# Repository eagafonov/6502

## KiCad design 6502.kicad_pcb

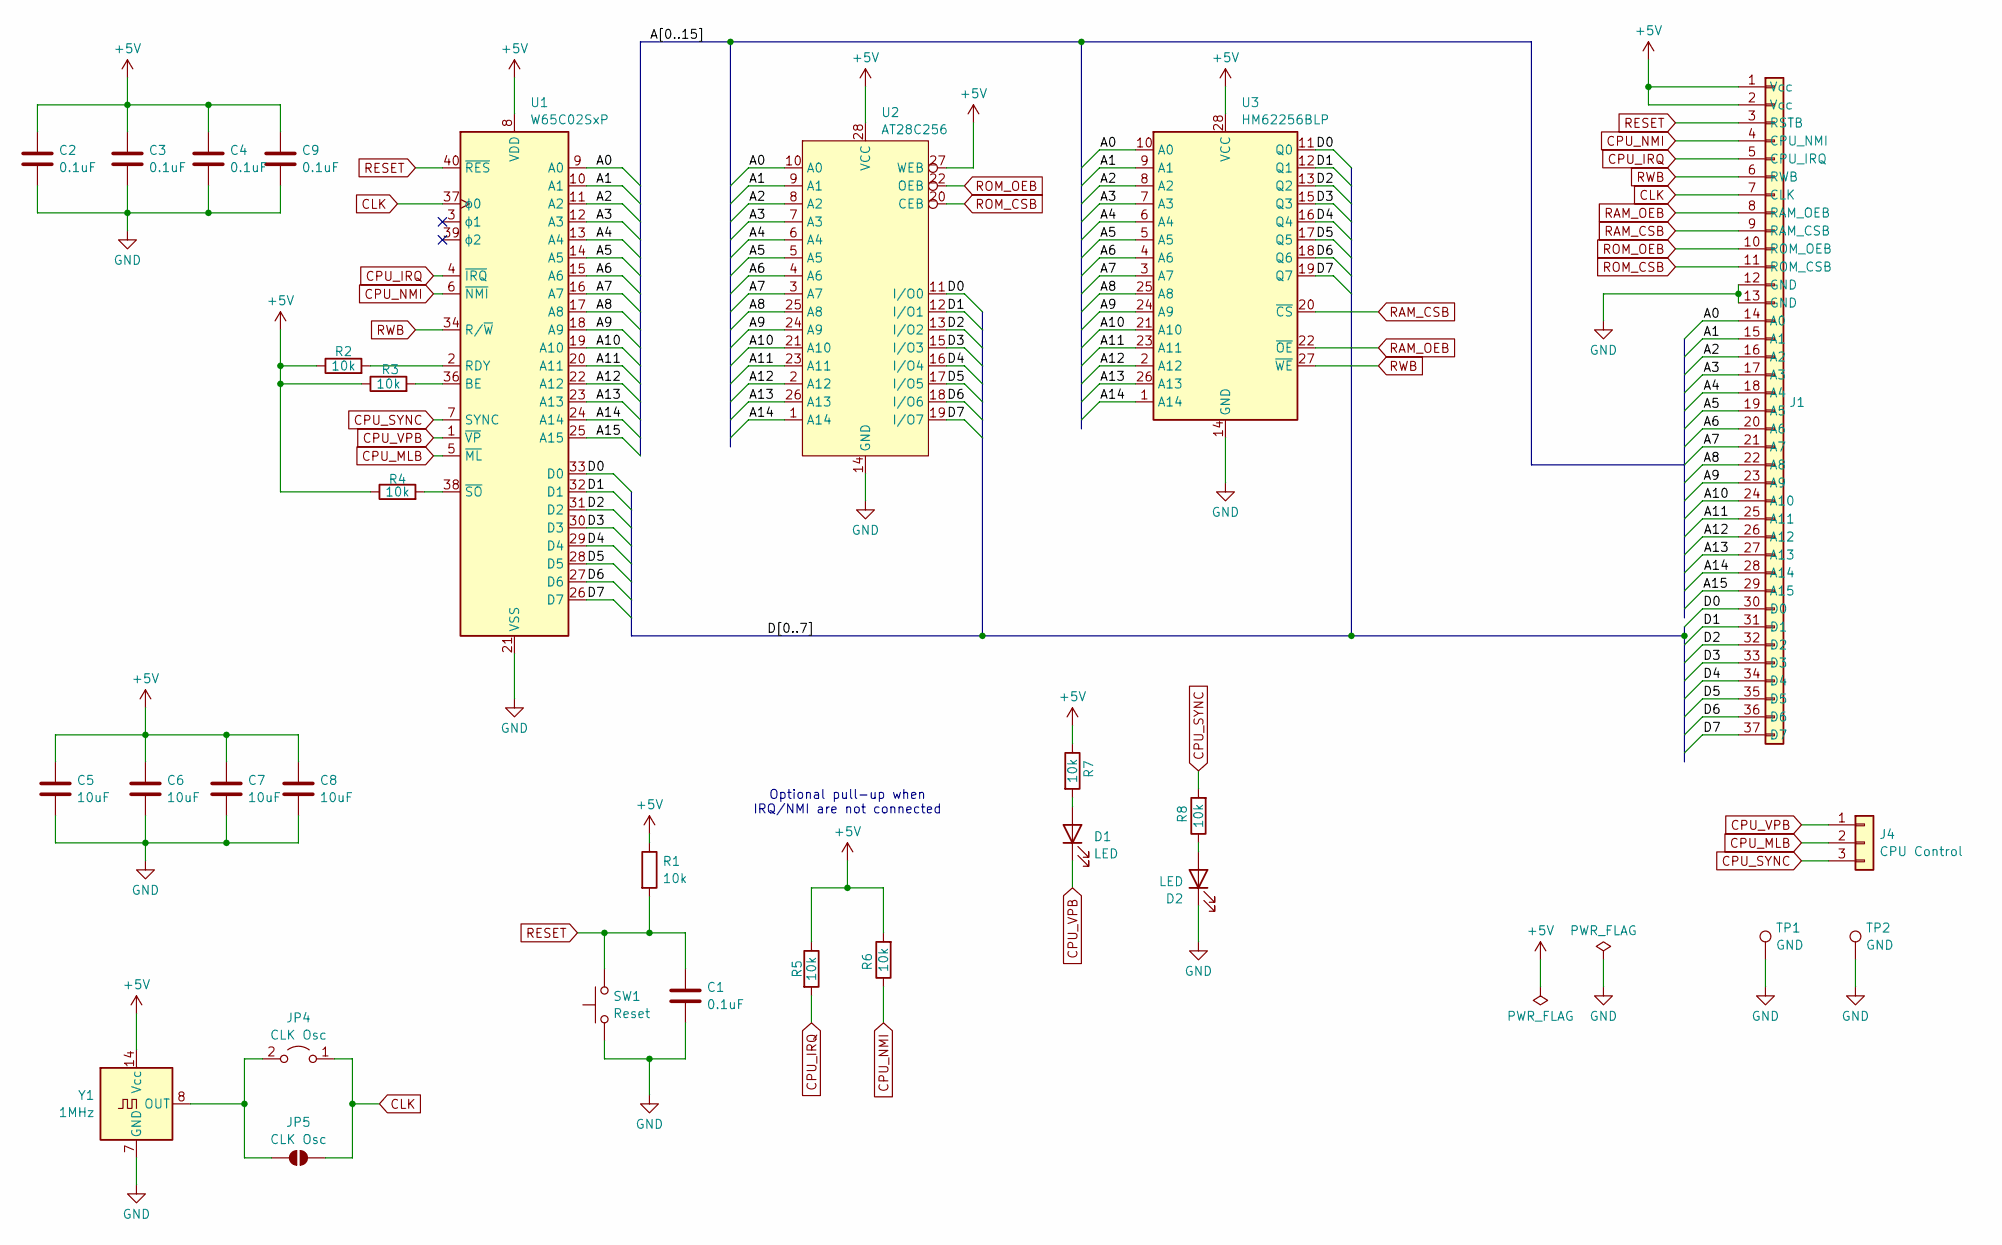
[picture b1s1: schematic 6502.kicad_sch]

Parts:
C1, C2, C3, C4, C9: 0.1uF; C_1206_3216Metric
C5, C6, C7, C8: 10uF; C_1206_3216Metric
D1, D2: LED; LED_D3.0mm_Horizontal_O1.27mm_Z2.0mm
J1: PinHeader_1x37_P2.54mm_Vertical
J4: CPU Control; PinHeader_1x03_P2.54mm_Vertical
JP4: CLK Osc; PinHeader_1x02_P2.54mm_Vertical
JP5: CLK Osc; SolderJumper-2_P1.3mm_Open_RoundedPad1.0x1.5mm
R1, R2, R3, R4, R5, R6, R7, R8: 10k; R_1206_3216Metric
SW1: Reset; SW_PUSH_6mm_TS_DO16
TP1, TP2: GND; TestPoint_Bridge_Pitch2.54mm_Drill0.7mm
U1: W65C02SxP; DIP-40_W15.24mm_Socket
U2: AT28C256; DIP_Socket-28_W11.9mm_W12.7mm_W15.24mm_W17.78mm_W18.5mm_3M_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
U3: HM62256BLP; DIP-28_W15.24mm_Socket
Y1: 1MHz; DIP-14_W7.62mm_Socket

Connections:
+5V: C2.1, C3.1, C4.1, C5.1, C6.1, C7.1, C8.1, C9.1, J1.1 (Vcc), J1.2 (Vcc), R1.1, R2.1, R3.1, R4.1, R5.1, R6.2, R7.1, U1.8 (VDD), U2.27 (WEB), U2.28 (VCC), U3.28 (VCC), Y1.14 (Vcc)
/A0: J1.14 (A0), U1.9 (A0), U2.10 (A0), U3.10 (A0)
/A1: J1.15 (A1), U1.10 (A1), U2.9 (A1), U3.9 (A1)
/A2: J1.16 (A2), U1.11 (A2), U2.8 (A2), U3.8 (A2)
/A3: J1.17 (A3), U1.12 (A3), U2.7 (A3), U3.7 (A3)
/A4: J1.18 (A4), U1.13 (A4), U2.6 (A4), U3.6 (A4)
/A5: J1.19 (A5), U1.14 (A5), U2.5 (A5), U3.5 (A5)
/A6: J1.20 (A6), U1.15 (A6), U2.4 (A6), U3.4 (A6)
/A7: J1.21 (A7), U1.16 (A7), U2.3 (A7), U3.3 (A7)
/A8: J1.22 (A8), U1.17 (A8), U2.25 (A8), U3.25 (A8)
/A9: J1.23 (A9), U1.18 (A9), U2.24 (A9), U3.24 (A9)
/A10: J1.24 (A10), U1.19 (A10), U2.21 (A10), U3.21 (A10)
/A11: J1.25 (A11), U1.20 (A11), U2.23 (A11), U3.23 (A11)
/A12: J1.26 (A12), U1.22 (A12), U2.2 (A12), U3.2 (A12)
/A13: J1.27 (A13), U1.23 (A13), U2.26 (A13), U3.26 (A13)
/A14: J1.28 (A14), U1.24 (A14), U2.1 (A14), U3.1 (A14)
/A15: J1.29 (A15), U1.25 (A15)
/D0: J1.30 (D0), U1.33 (D0), U2.11 (I/O0), U3.11 (Q0)
/D1: J1.31 (D1), U1.32 (D1), U2.12 (I/O1), U3.12 (Q1)
/D2: J1.32 (D2), U1.31 (D2), U2.13 (I/O2), U3.13 (Q2)
/D3: J1.33 (D3), U1.30 (D3), U2.15 (I/O3), U3.15 (Q3)
/D4: J1.34 (D4), U1.29 (D4), U2.16 (I/O4), U3.16 (Q4)
/D5: J1.35 (D5), U1.28 (D5), U2.17 (I/O5), U3.17 (Q5)
/D6: J1.36 (D6), U1.27 (D6), U2.18 (I/O6), U3.18 (Q6)
/D7: J1.37 (D7), U1.26 (D7), U2.19 (I/O7), U3.19 (Q7)
CLK: J1.7 (CLK), JP4.1 (A), JP5.1 (A), U1.37 (ϕ0)
CPU_IRQ: J1.5 (CPU_IRQ), R5.2, U1.4 (~IRQ)
CPU_MLB: J4.2, U1.5 (~ML)
CPU_NMI: J1.4 (CPU_NMI), R6.1, U1.6 (~NMI)
CPU_SYNC: J4.3, R8.2, U1.7 (SYNC)
CPU_VPB: D1.1 (K), J4.1, U1.1 (~VP)
GND: C1.2, C2.2, C3.2, C4.2, C5.2, C6.2, C7.2, C8.2, C9.2, D2.1 (K), J1.12 (GND), J1.13 (GND), SW1.1, TP1.1, TP2.1, U1.21 (VSS), U2.14 (GND), U3.14 (GND), Y1.7 (GND)
unnamed: D1.2 (A), R7.2
unnamed: D2.2 (A), R8.1
unnamed: JP4.2 (B), JP5.2 (B), Y1.8 (OUT)
unnamed: R3.2, U1.36 (BE)
unnamed: R2.2, U1.2 (RDY)
unnamed: R4.2, U1.38 (~SO)
RAM_CSB: J1.9 (RAM_CSB), U3.20 (~CS)
RAM_OEB: J1.8 (RAM_OEB), U3.22 (~OE)
RESET: C1.1, J1.3 (RSTB), R1.2, SW1.2, U1.40 (~RES)
ROM_CSB: J1.11 (ROM_CSB), U2.20 (CEB)
ROM_OEB: J1.10 (ROM_OEB), U2.22 (OEB)
RWB: J1.6 (RWB), U1.34 (R/~W), U3.27 (~WE)

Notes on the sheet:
Optional pull-up when IRQ/NMI are not connected

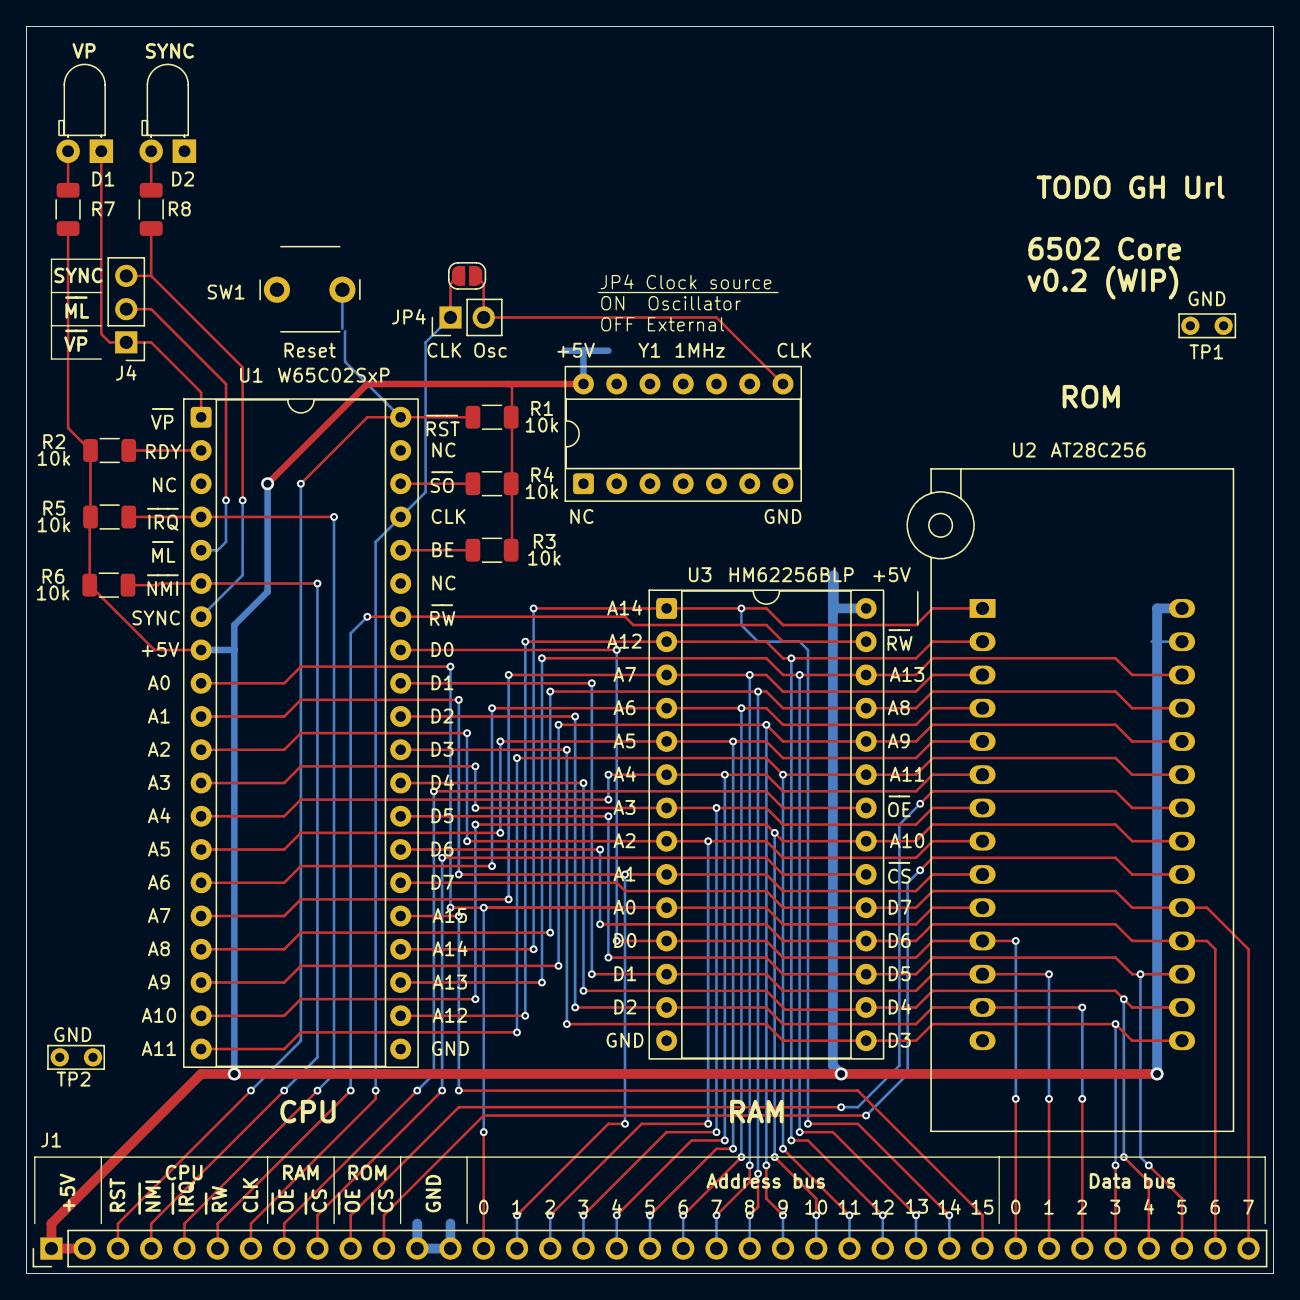
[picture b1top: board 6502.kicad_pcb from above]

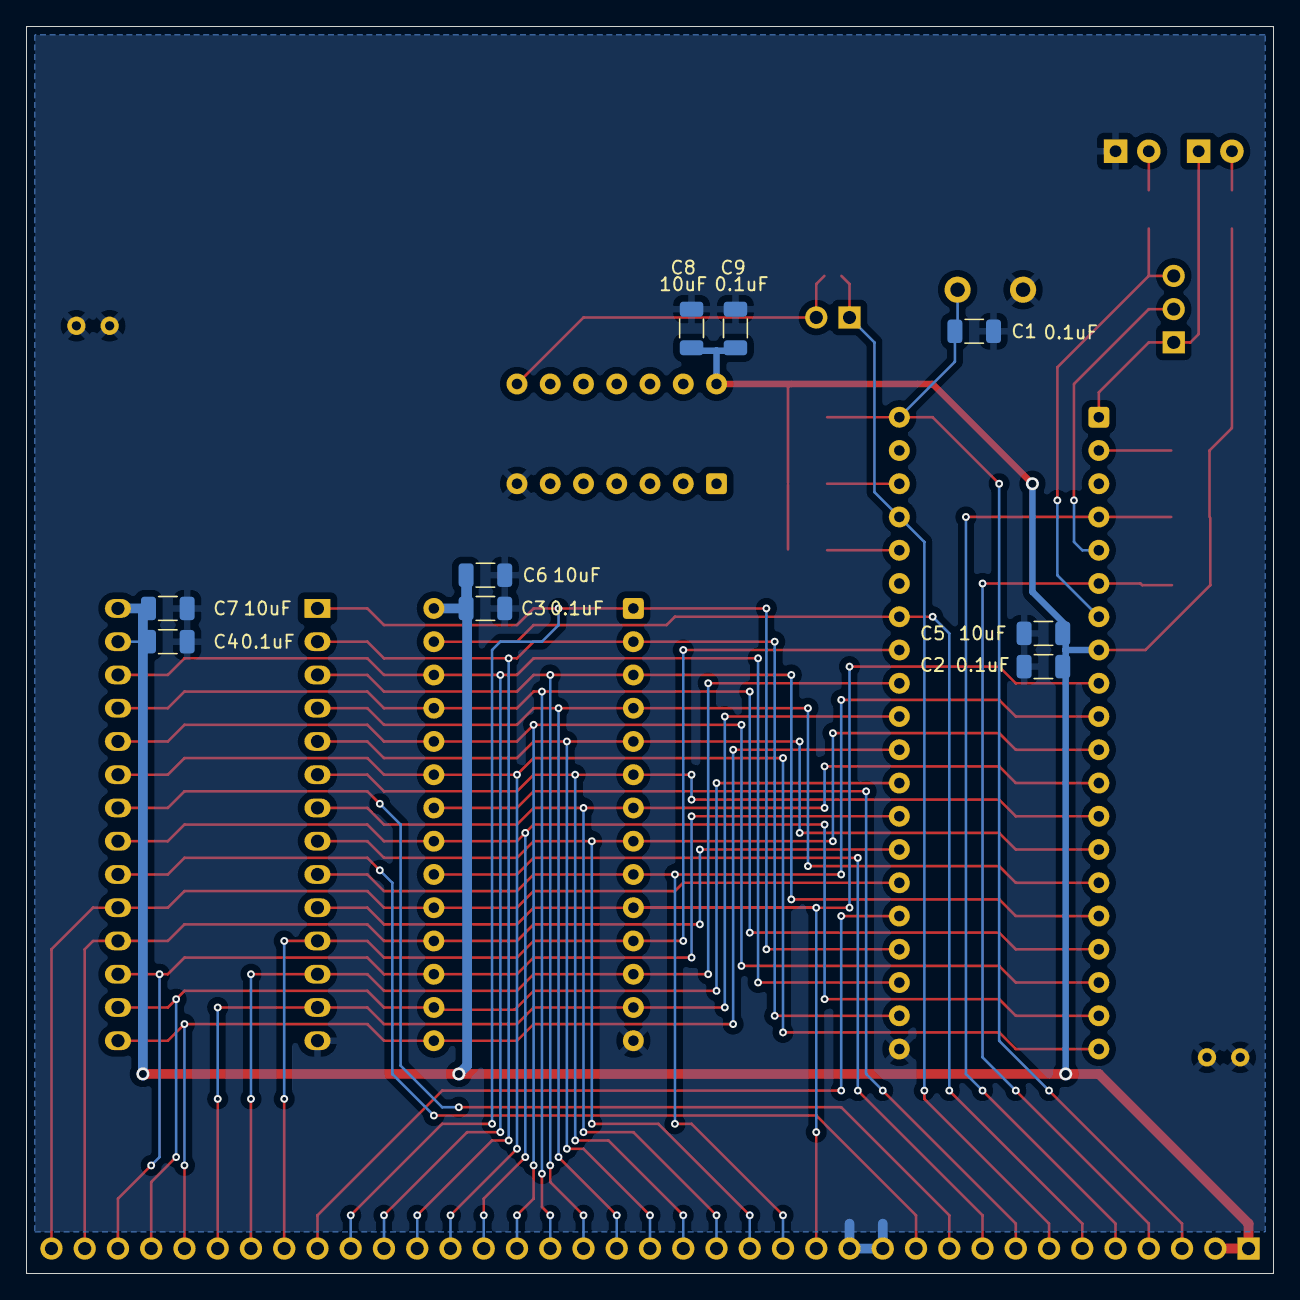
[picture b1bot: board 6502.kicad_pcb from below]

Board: 2 copper layers, 95.2 x 95.3 mm, 30 parts (9 on the bottom side), 44 nets.

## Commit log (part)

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2025-12-28 Initial version (v0.1) + gerber files
2025-12-28 Add PCB 3D images
2025-12-28 6502.kicad_pro: Fix a few post-production issues
    Fixed a few issues found on the v0.1 boards:
    - J3: Fix misplaced CLK/RW/NMI/IRQ CPU labels
    - J3: Fix CE->CS for both RAM and ROM
    - J3: Move via next to A0 for more solid BG ground polygon
    - J4: Reroute on the front for more solid BG ground polygon
    - RAM: Move vias out of OE and CS F.silk
2026-01-17 Update schematics
    Schematics:
    - J3: Replace SYNC with RST
    - J4: Add SYNC
    - Rename CEB do CSB (Chip Enabled -> Chip Select)
    PCB:
    - Increase GND Polygon min clearance
2026-01-17 pcb: Move CPU/ROM/RAM Text labels
